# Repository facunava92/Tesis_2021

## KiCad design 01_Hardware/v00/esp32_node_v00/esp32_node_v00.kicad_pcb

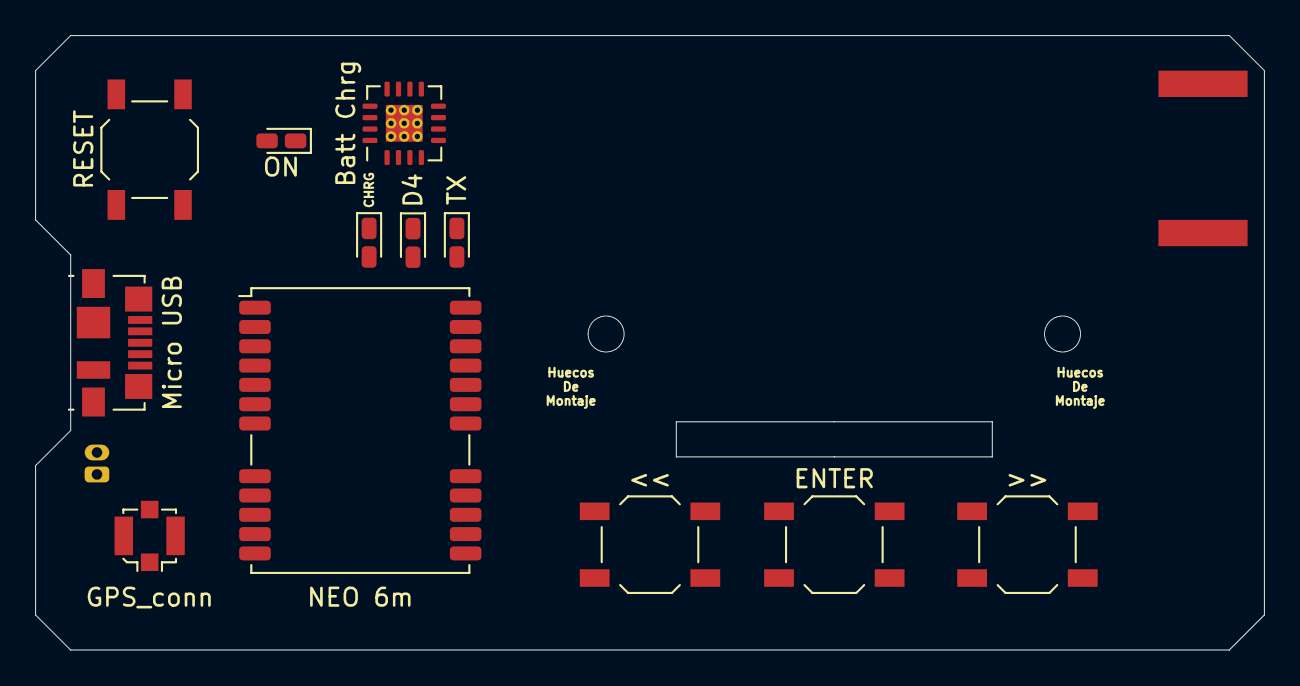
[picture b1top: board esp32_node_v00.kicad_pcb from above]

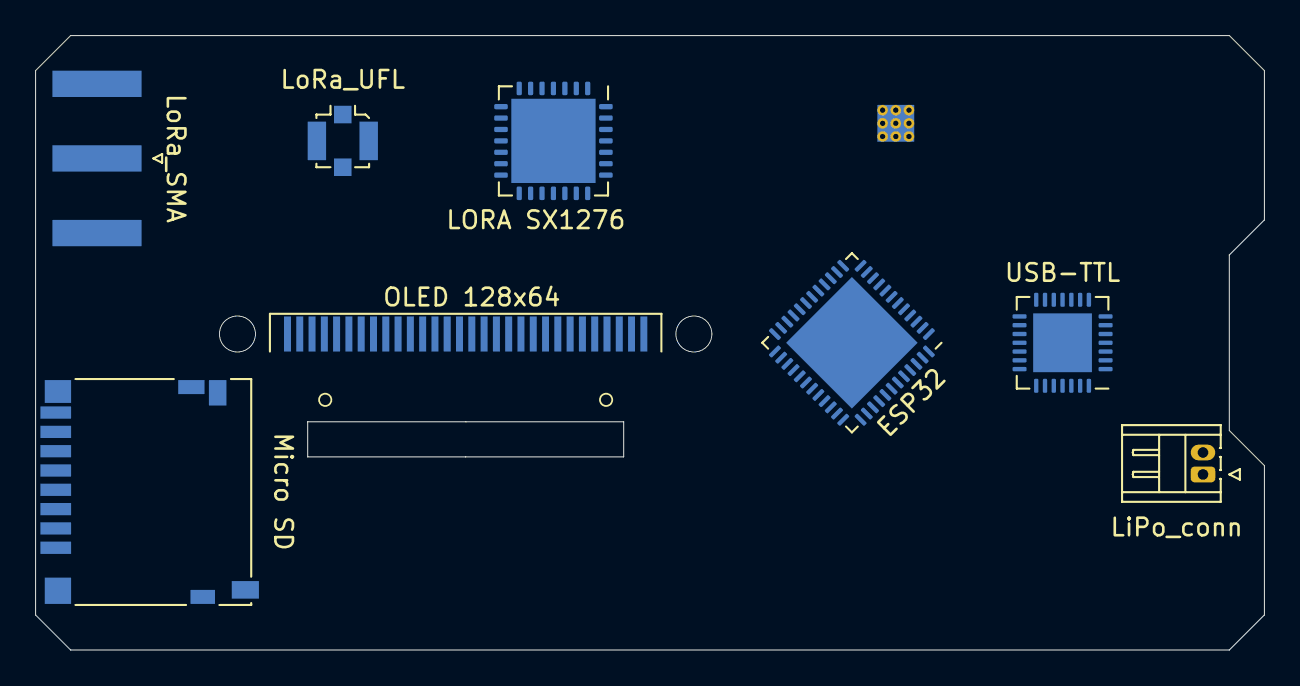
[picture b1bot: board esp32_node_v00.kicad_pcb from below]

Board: 2 copper layers, 70.0 x 35.0 mm, 20 parts (8 on the bottom side), 7 nets, no tracks yet.

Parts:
<<: SW_SPST_TL3342
>>: SW_SPST_TL3342
Batt Chrg: LTC4055-1; QFN-16-1EP_4x4mm_P0.65mm_EP2.1x2.1mm_ThermalVias
CHRG: LED; LED_0603_1608Metric_Castellated
D4: LED; LED_0603_1608Metric_Castellated
ENTER: SW_SPST_TL3342
ESP32: ESP32-PICO-D4; QFN-48-1EP_7x7mm_P0.5mm_EP5.3x5.3mm
GPS_conn: U.FL_Molex_MCRF_73412-0110_Vertical
LORA SX1276: SX1273; QFN-28-1EP_6x6mm_P0.65mm_EP4.8x4.8mm
LiPo_conn: Hirose_DF13-02P-1.25DS_1x02_P1.25mm_Horizontal
LoRa_SMA: SMA_Amphenol_132289_EdgeMount
LoRa_UFL: U.FL_Molex_MCRF_73412-0110_Vertical
Micro SD: microSD_HC_Hirose_DM3D-SF
Micro USB: USB_B_Micro; USB_Micro-B_Molex_47346-0001
NEO 6m: NEO-M8M; ublox_NEO
OLED 128x64: Conn_01x30; OLED-128O064D
ON: LED; LED_0603_1608Metric_Castellated
RESET: SW_SPST_TL3342
TX: LED; LED_0603_1608Metric_Castellated
USB-TTL: CP2102N-A01-GQFN28; QFN-28-1EP_5x5mm_P0.5mm_EP3.35x3.35mm

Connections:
unnamed: LORA SX1276.16, LORA SX1276.22, LORA SX1276.26
unnamed: Batt Chrg.1, Batt Chrg.4
unnamed: Batt Chrg.10, Batt Chrg.17
unnamed: USB-TTL.3, USB-TTL.29
unnamed: ESP32.1, ESP32.43, ESP32.46
unnamed: ESP32.3, ESP32.4
unnamed: NEO 6m.10, NEO 6m.12, NEO 6m.13, NEO 6m.24

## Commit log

2021-04-05 Agrego carpeta de Preproyecto con diagrama en bloque
2021-04-06 agrego preproyectos de otros
2021-04-07 Primera Organizacion
2021-04-07 Add files via upload
    Cucha, tema Brujula le metemos, estaría bien describir todo como funcionaria?
2021-04-07 Add files via upload
    Che, tema funcionamiento, poner todo? Brujula con calculo de distancia y direccion cardinal?
2021-04-08 Agrego Libros
2021-04-11 Agrego primer codigo de OLED UiDemo
2021-04-12 Agrego avance de BootScreen
2021-04-14 Actualizo algo de Hw desde Asus
2021-04-14 Add files via upload
    Checkear modificacion
2021-04-14 Add files via upload
    14/04/2021
2021-04-14 Add files via upload
    Miralo
2021-04-15 NaNo Device
2021-04-15 Actualizo v00, preproyecto
